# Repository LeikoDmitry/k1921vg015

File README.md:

# Микроконтроллер К1921ВГ015 на базе ядра архитектуры RISC-V

Отладочная плата микроконтроллера K1921VG015

## Номиналы конденсаторов
- C1 - 47uf
- C2 - 0.1uf,
- C3 / C5 - 22uf
- C6 / C9 - 20pf
- C10 / C14 - 0.1uf

## Номиналы индуктивностей L1 - L4 и резистора R10
- R10 = 100/300ом

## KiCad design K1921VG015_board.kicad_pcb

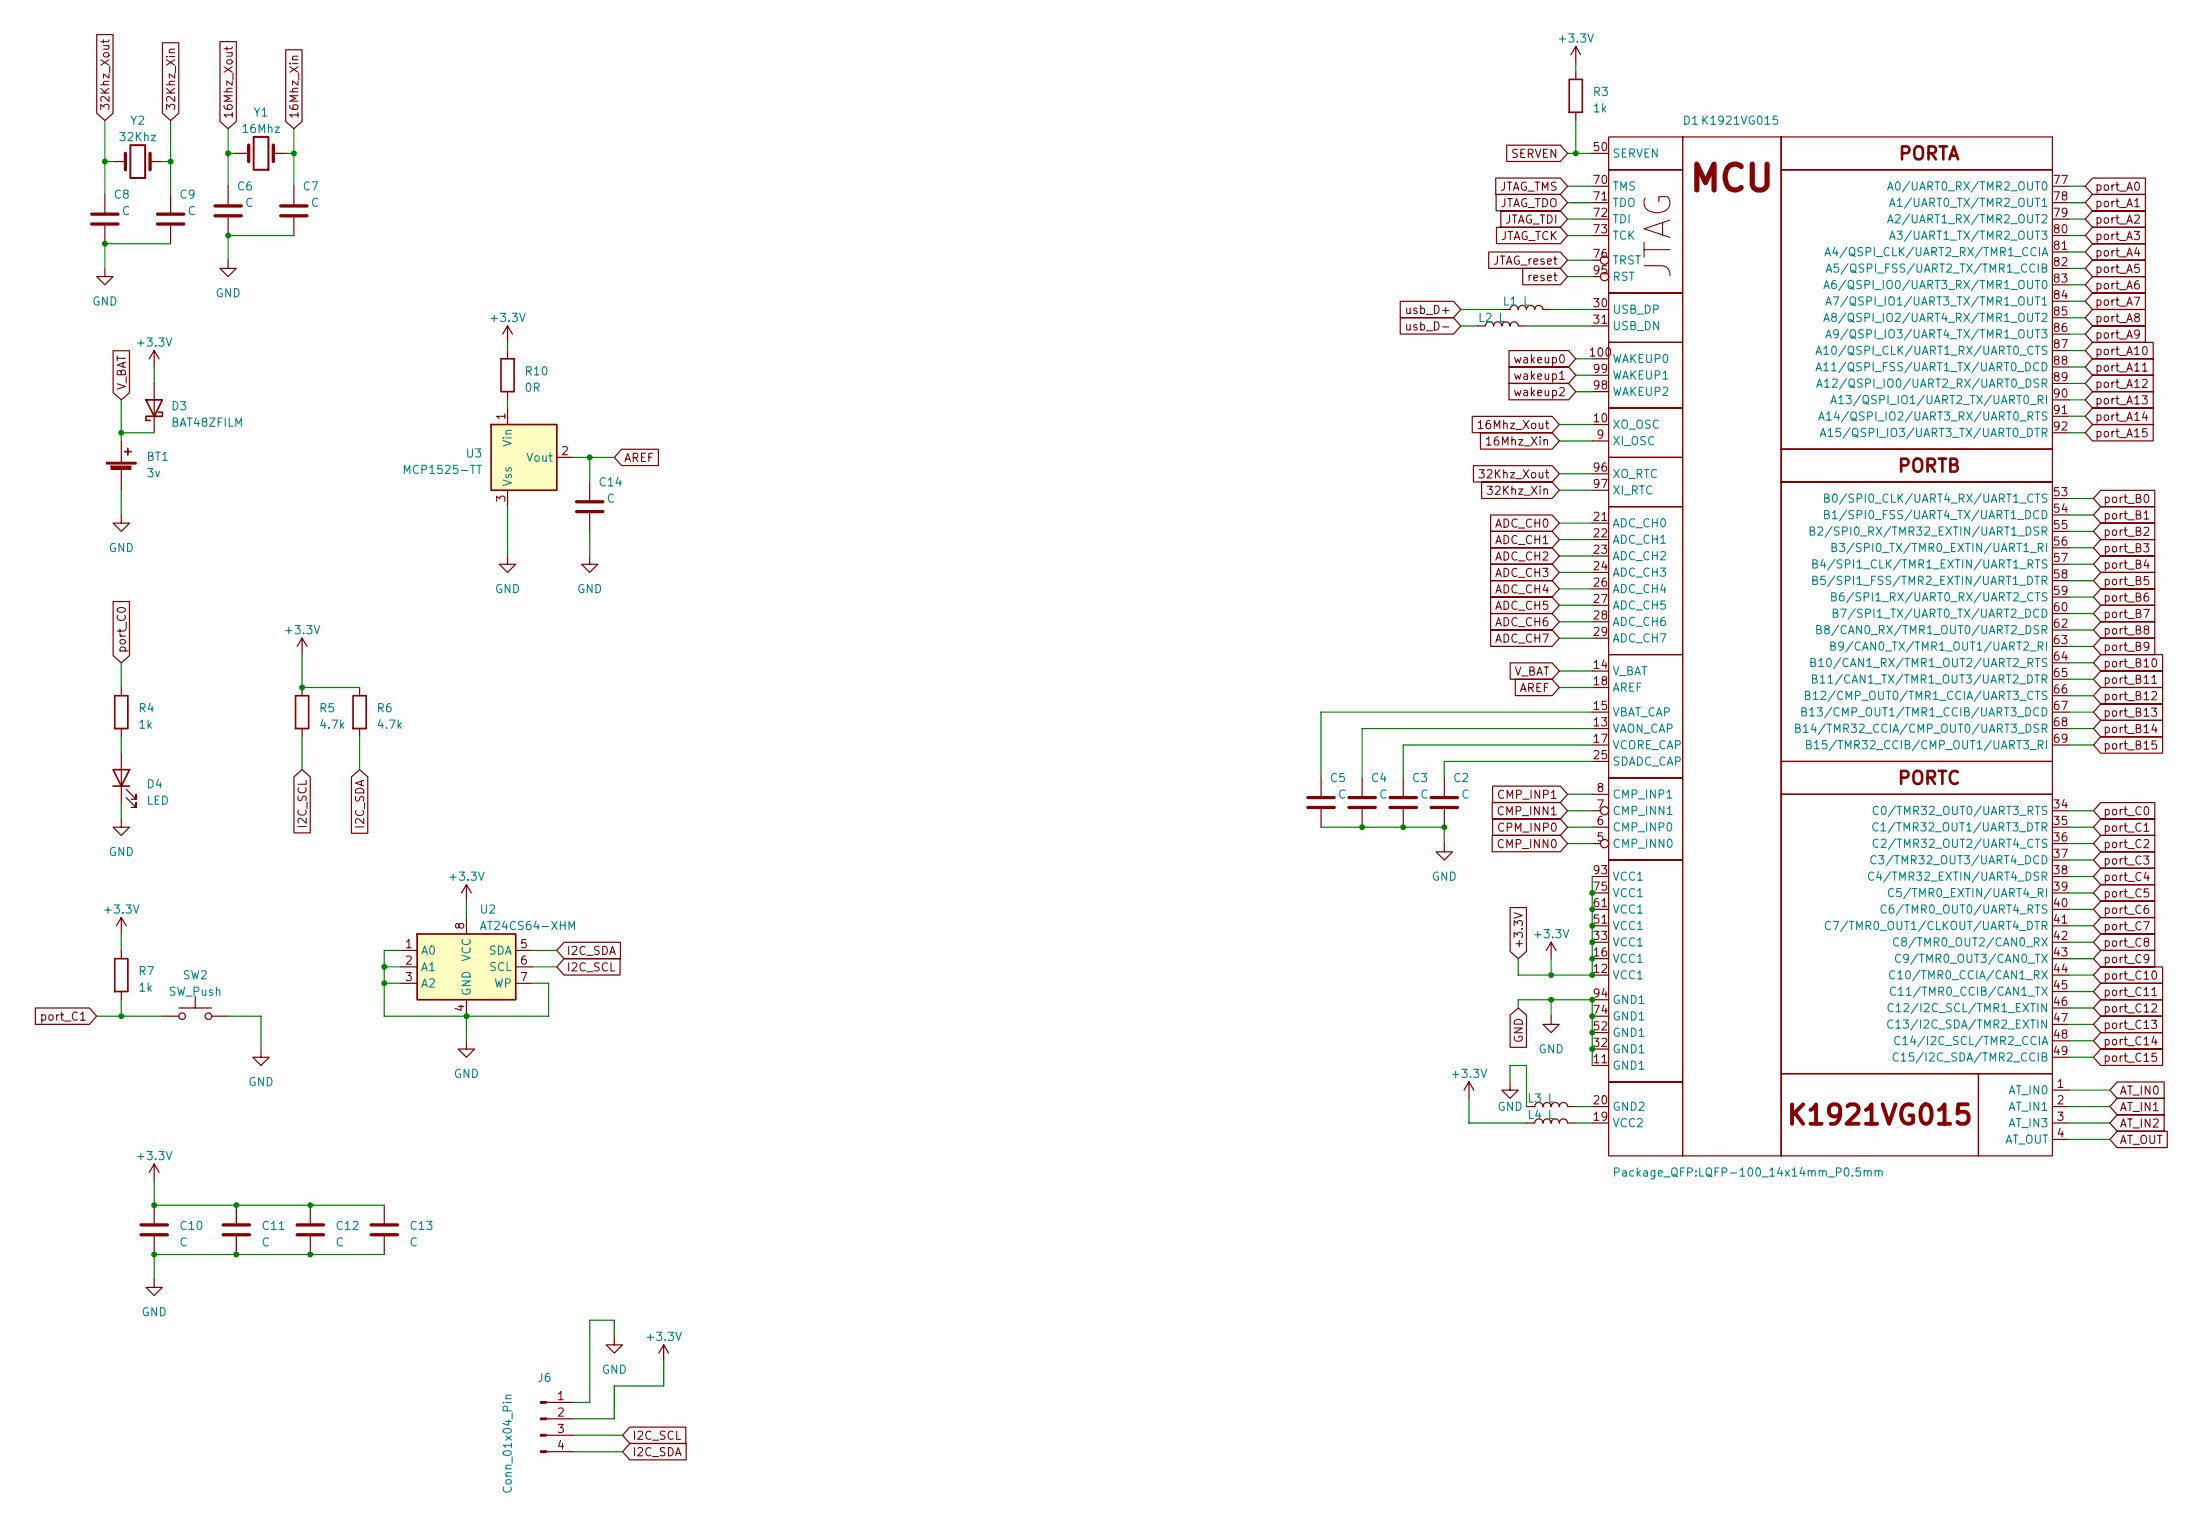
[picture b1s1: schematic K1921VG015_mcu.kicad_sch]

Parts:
BT1: 3v; BatteryHolder_Keystone_1058_1x2032
C2, C6, C7, C8, C9, C10, C11, C12, C13, C14: C; C_0805_2012Metric
C3, C4, C5: C; CP_EIA-3216-18_Kemet-A
D1: K1921VG015; LQFP-100_14x14mm_P0.5mm
D3: BAT48ZFILM; D_SOD-123
D4: LED; LED_0805_2012Metric
J6: Conn_01x04_Pin; PinHeader_1x04_P2.54mm_Vertical
L1, L2, L3, L4: L; L_0805_2012Metric
R3, R4, R7: 1k; R_0805_2012Metric
R5, R6: 4.7k; R_0805_2012Metric
R10: 0R; R_0805_2012Metric
SW2: SW_Push; SW_Push_1P1T_NO_6x6mm_H9.5mm
U2: AT24CS64-XHM; TSSOP-8_4.4x3mm_P0.65mm
U3: MCP1525-TT; SOT-23
Y1: 16Mhz; Crystal_SMD_5032-2Pin_5.0x3.2mm
Y2: 32Khz; Crystal_SMD_3215-2Pin_3.2x1.5mm

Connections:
16Mhz_Xin: C7.1, D1.9 (XI_OSC), Y1.1
16Mhz_Xout: C6.1, D1.10 (XO_OSC), Y1.2
32Khz_Xin: C9.1, D1.97 (XI_RTC), Y2.1
32Khz_Xout: C8.1, D1.96 (XO_RTC), Y2.2
+3.3V: C10.1, C11.1, C12.1, C13.1, D1.12 (VCC1), D1.16 (VCC1), D1.33 (VCC1), D1.51 (VCC1), D1.61 (VCC1), D1.75 (VCC1), D1.93 (VCC1), D3.2 (A), J6.2, L4.1, R3.1, R5.1, R6.1, R7.1, R10.2, U2.8 (VCC); also elsewhere on the board
ADC_CH0: D1.21 (ADC_CH0); also elsewhere on the board
ADC_CH1: D1.22 (ADC_CH1); also elsewhere on the board
ADC_CH2: D1.23 (ADC_CH2); also elsewhere on the board
ADC_CH3: D1.24 (ADC_CH3); also elsewhere on the board
ADC_CH4: D1.26 (ADC_CH4); also elsewhere on the board
ADC_CH5: D1.27 (ADC_CH5); also elsewhere on the board
ADC_CH6: D1.28 (ADC_CH6); also elsewhere on the board
ADC_CH7: D1.29 (ADC_CH7); also elsewhere on the board
AREF: C14.1, D1.18 (AREF), U3.2 (Vout)
AT_IN0: D1.1 (AT_IN0); also elsewhere on the board
AT_IN1: D1.2 (AT_IN1); also elsewhere on the board
AT_IN2: D1.3 (AT_IN3); also elsewhere on the board
AT_OUT: D1.4 (AT_OUT); also elsewhere on the board
CMP_INN0: D1.5 (CMP_INN0); also elsewhere on the board
CMP_INN1: D1.7 (CMP_INN1); also elsewhere on the board
CMP_INP1: D1.8 (CMP_INP1); also elsewhere on the board
CPM_INP0: D1.6 (CMP_INP0); also elsewhere on the board
GND: BT1.2 (-), C2.2, C3.2, C4.2, C5.2, C6.2, C7.2, C8.2, C9.2, C10.2, C11.2, C12.2, C13.2, C14.2, D1.11 (GND1), D1.32 (GND1), D1.52 (GND1), D1.74 (GND1), D1.94 (GND1), D4.1 (K), J6.1, L3.1, SW2.2, U2.1 (A0), U2.2 (A1), U2.3 (A2), U2.4 (GND), U2.7 (WP), U3.3 (Vss); also elsewhere on the board
I2C_SCL: J6.3, R5.2, U2.6 (SCL); also elsewhere on the board
I2C_SDA: J6.4, R6.2, U2.5 (SDA); also elsewhere on the board
JTAG_TCK: D1.73 (TCK); also elsewhere on the board
JTAG_TDI: D1.72 (TDI); also elsewhere on the board
JTAG_TDO: D1.71 (TDO); also elsewhere on the board
JTAG_TMS: D1.70 (TMS); also elsewhere on the board
JTAG_reset: D1.76 (TRST); also elsewhere on the board
unnamed: D1.20 (GND2), L3.2
unnamed: C2.1, D1.25 (SDADC_CAP)
unnamed: D1.31 (USB_DN), L2.2
unnamed: D1.30 (USB_DP), L1.2
unnamed: C4.1, D1.13 (VAON_CAP)
unnamed: C5.1, D1.15 (VBAT_CAP)
unnamed: D1.19 (VCC2), L4.2
unnamed: C3.1, D1.17 (VCORE_CAP)
unnamed: D4.2 (A), R4.2
unnamed: R10.1, U3.1 (Vin)
SERVEN: D1.50 (SERVEN), R3.2; also elsewhere on the board
V_BAT: BT1.1 (+), D1.14 (V_BAT), D3.1 (K)
port_A0: D1.77 (A0/UART0_RX/TMR2_OUT0); also elsewhere on the board
port_A1: D1.78 (A1/UART0_TX/TMR2_OUT1); also elsewhere on the board
port_A2: D1.79 (A2/UART1_RX/TMR2_OUT2); also elsewhere on the board
port_A3: D1.80 (A3/UART1_TX/TMR2_OUT3); also elsewhere on the board
port_A4: D1.81 (A4/QSPI_CLK/UART2_RX/TMR1_CCIA); also elsewhere on the board
port_A5: D1.82 (A5/QSPI_FSS/UART2_TX/TMR1_CCIB); also elsewhere on the board
port_A6: D1.83 (A6/QSPI_IO0/UART3_RX/TMR1_OUT0); also elsewhere on the board
port_A7: D1.84 (A7/QSPI_IO1/UART3_TX/TMR1_OUT1); also elsewhere on the board
port_A8: D1.85 (A8/QSPI_IO2/UART4_RX/TMR1_OUT2); also elsewhere on the board
port_A9: D1.86 (A9/QSPI_IO3/UART4_TX/TMR1_OUT3); also elsewhere on the board
port_A10: D1.87 (A10/QSPI_CLK/UART1_RX/UART0_CTS); also elsewhere on the board
port_A11: D1.88 (A11/QSPI_FSS/UART1_TX/UART0_DCD); also elsewhere on the board
port_A12: D1.89 (A12/QSPI_IO0/UART2_RX/UART0_DSR); also elsewhere on the board
port_A13: D1.90 (A13/QSPI_IO1/UART2_TX/UART0_RI); also elsewhere on the board
port_A14: D1.91 (A14/QSPI_IO2/UART3_RX/UART0_RTS); also elsewhere on the board
port_A15: D1.92 (A15/QSPI_IO3/UART3_TX/UART0_DTR); also elsewhere on the board
port_B0: D1.53 (B0/SPI0_CLK/UART4_RX/UART1_CTS); also elsewhere on the board
port_B1: D1.54 (B1/SPI0_FSS/UART4_TX/UART1_DCD); also elsewhere on the board
port_B2: D1.55 (B2/SPI0_RX/TMR32_EXTIN/UART1_DSR); also elsewhere on the board
port_B3: D1.56 (B3/SPI0_TX/TMR0_EXTIN/UART1_RI); also elsewhere on the board
port_B4: D1.57 (B4/SPI1_CLK/TMR1_EXTIN/UART1_RTS); also elsewhere on the board
port_B5: D1.58 (B5/SPI1_FSS/TMR2_EXTIN/UART1_DTR); also elsewhere on the board
port_B6: D1.59 (B6/SPI1_RX/UART0_RX/UART2_CTS); also elsewhere on the board
port_B7: D1.60 (B7/SPI1_TX/UART0_TX/UART2_DCD); also elsewhere on the board
port_B8: D1.62 (B8/CAN0_RX/TMR1_OUT0/UART2_DSR); also elsewhere on the board
port_B9: D1.63 (B9/CAN0_TX/TMR1_OUT1/UART2_RI); also elsewhere on the board
port_B10: D1.64 (B10/CAN1_RX/TMR1_OUT2/UART2_RTS); also elsewhere on the board
port_B11: D1.65 (B11/CAN1_TX/TMR1_OUT3/UART2_DTR); also elsewhere on the board
port_B12: D1.66 (B12/CMP_OUT0/TMR1_CCIA/UART3_CTS); also elsewhere on the board
port_B13: D1.67 (B13/CMP_OUT1/TMR1_CCIB/UART3_DCD); also elsewhere on the board
port_B14: D1.68 (B14/TMR32_CCIA/CMP_OUT0/UART3_DSR); also elsewhere on the board
port_B15: D1.69 (B15/TMR32_CCIB/CMP_OUT1/UART3_RI); also elsewhere on the board
port_C0: D1.34 (С0/TMR32_OUT0/UART3_RTS), R4.1; also elsewhere on the board
port_C1: D1.35 (С1/TMR32_OUT1/UART3_DTR), R7.2, SW2.1; also elsewhere on the board
port_C2: D1.36 (С2/TMR32_OUT2/UART4_CTS); also elsewhere on the board
port_C3: D1.37 (С3/TMR32_OUT3/UART4_DCD); also elsewhere on the board
port_C4: D1.38 (С4/TMR32_EXTIN/UART4_DSR); also elsewhere on the board
port_C5: D1.39 (С5/TMR0_EXTIN/UART4_RI); also elsewhere on the board
port_C6: D1.40 (С6/TMR0_OUT0/UART4_RTS); also elsewhere on the board
port_C7: D1.41 (С7/TMR0_OUT1/CLKOUT/UART4_DTR); also elsewhere on the board
port_C8: D1.42 (С8/TMR0_OUT2/CAN0_RX); also elsewhere on the board
port_C9: D1.43 (С9/TMR0_OUT3/CAN0_TX); also elsewhere on the board
port_C10: D1.44 (С10/TMR0_CCIA/CAN1_RX); also elsewhere on the board
port_C11: D1.45 (С11/TMR0_CCIB/CAN1_TX); also elsewhere on the board
port_C12: D1.46 (С12/I2C_SCL/TMR1_EXTIN); also elsewhere on the board
port_C13: D1.47 (С13/I2C_SDA/TMR2_EXTIN); also elsewhere on the board
port_C14: D1.48 (С14/I2C_SCL/TMR2_CCIA); also elsewhere on the board
port_C15: D1.49 (С15/I2C_SDA/TMR2_CCIB); also elsewhere on the board
reset: D1.95 (RST); also elsewhere on the board
usb_D+: L1.1; also elsewhere on the board
usb_D-: L2.1; also elsewhere on the board
wakeup0: D1.100 (WAKEUP0); also elsewhere on the board
wakeup1: D1.99 (WAKEUP1); also elsewhere on the board
wakeup2: D1.98 (WAKEUP2); also elsewhere on the board

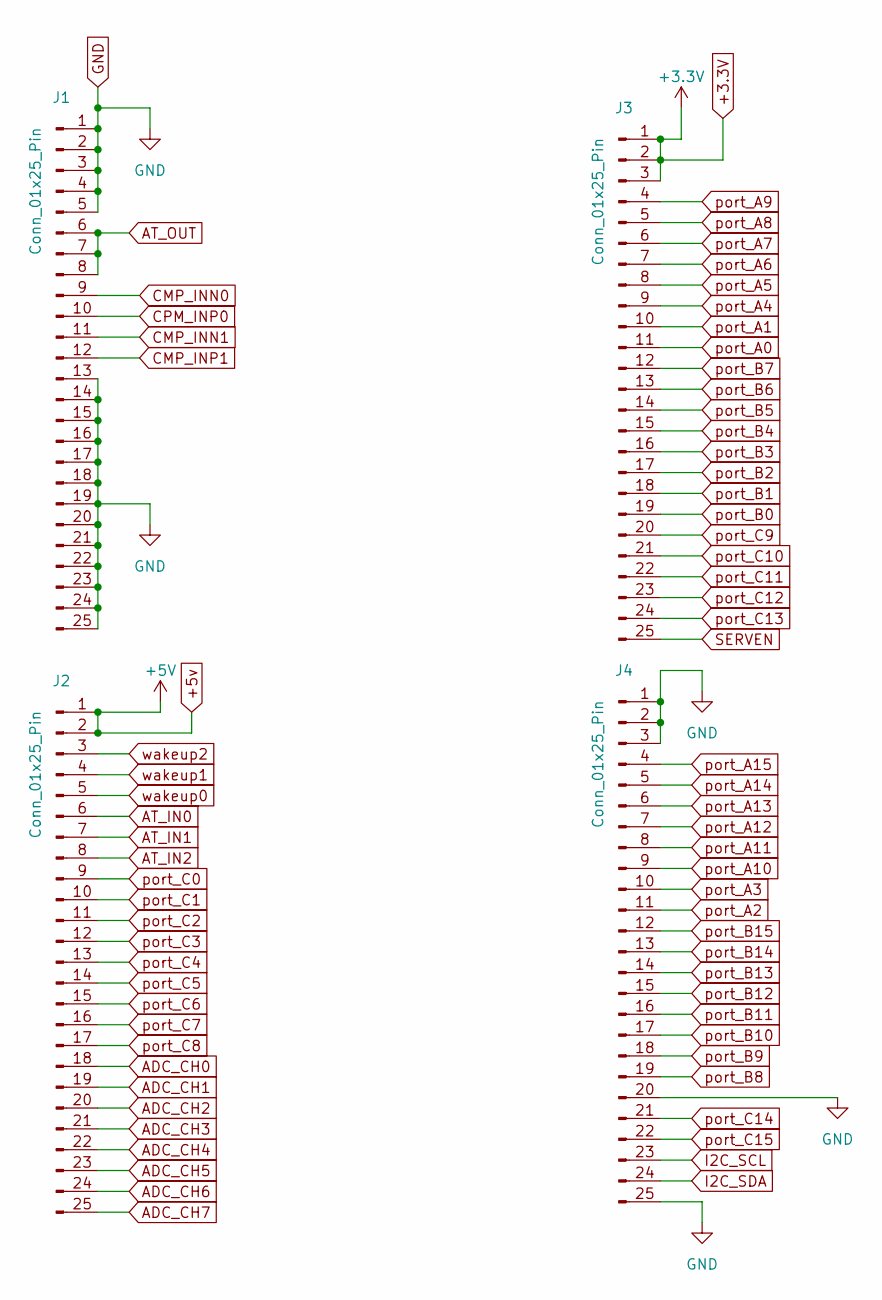
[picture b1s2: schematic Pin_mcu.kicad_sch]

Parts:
J1, J2, J3, J4: Conn_01x25_Pin; PinHeader_1x25_P2.54mm_Vertical

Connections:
+3.3V: J3.1, J3.2, J3.3; also elsewhere on the board
+5v: J2.1, J2.2; also elsewhere on the board
ADC_CH0: J2.18; also elsewhere on the board
ADC_CH1: J2.19; also elsewhere on the board
ADC_CH2: J2.20; also elsewhere on the board
ADC_CH3: J2.21; also elsewhere on the board
ADC_CH4: J2.22; also elsewhere on the board
ADC_CH5: J2.23; also elsewhere on the board
ADC_CH6: J2.24; also elsewhere on the board
ADC_CH7: J2.25; also elsewhere on the board
AT_IN0: J2.6; also elsewhere on the board
AT_IN1: J2.7; also elsewhere on the board
AT_IN2: J2.8; also elsewhere on the board
AT_OUT: J1.6, J1.7, J1.8; also elsewhere on the board
CMP_INN0: J1.9; also elsewhere on the board
CMP_INN1: J1.11; also elsewhere on the board
CMP_INP1: J1.12; also elsewhere on the board
CPM_INP0: J1.10; also elsewhere on the board
GND: J1.1, J1.2, J1.3, J1.4, J1.5, J1.13, J1.14, J1.15, J1.16, J1.17, J1.18, J1.19, J1.20, J1.21, J1.22, J1.23, J1.24, J1.25, J4.1, J4.2, J4.3, J4.20, J4.25; also elsewhere on the board
I2C_SCL: J4.23; also elsewhere on the board
I2C_SDA: J4.24; also elsewhere on the board
SERVEN: J3.25; also elsewhere on the board
port_A0: J3.11; also elsewhere on the board
port_A1: J3.10; also elsewhere on the board
port_A2: J4.11; also elsewhere on the board
port_A3: J4.10; also elsewhere on the board
port_A4: J3.9; also elsewhere on the board
port_A5: J3.8; also elsewhere on the board
port_A6: J3.7; also elsewhere on the board
port_A7: J3.6; also elsewhere on the board
port_A8: J3.5; also elsewhere on the board
port_A9: J3.4; also elsewhere on the board
port_A10: J4.9; also elsewhere on the board
port_A11: J4.8; also elsewhere on the board
port_A12: J4.7; also elsewhere on the board
port_A13: J4.6; also elsewhere on the board
port_A14: J4.5; also elsewhere on the board
port_A15: J4.4; also elsewhere on the board
port_B0: J3.19; also elsewhere on the board
port_B1: J3.18; also elsewhere on the board
port_B2: J3.17; also elsewhere on the board
port_B3: J3.16; also elsewhere on the board
port_B4: J3.15; also elsewhere on the board
port_B5: J3.14; also elsewhere on the board
port_B6: J3.13; also elsewhere on the board
port_B7: J3.12; also elsewhere on the board
port_B8: J4.19; also elsewhere on the board
port_B9: J4.18; also elsewhere on the board
port_B10: J4.17; also elsewhere on the board
port_B11: J4.16; also elsewhere on the board
port_B12: J4.15; also elsewhere on the board
port_B13: J4.14; also elsewhere on the board
port_B14: J4.13; also elsewhere on the board
port_B15: J4.12; also elsewhere on the board
port_C0: J2.9; also elsewhere on the board
port_C1: J2.10; also elsewhere on the board
port_C2: J2.11; also elsewhere on the board
port_C3: J2.12; also elsewhere on the board
port_C4: J2.13; also elsewhere on the board
port_C5: J2.14; also elsewhere on the board
port_C6: J2.15; also elsewhere on the board
port_C7: J2.16; also elsewhere on the board
port_C8: J2.17; also elsewhere on the board
port_C9: J3.20; also elsewhere on the board
port_C10: J3.21; also elsewhere on the board
port_C11: J3.22; also elsewhere on the board
port_C12: J3.23; also elsewhere on the board
port_C13: J3.24; also elsewhere on the board
port_C14: J4.21; also elsewhere on the board
port_C15: J4.22; also elsewhere on the board
wakeup0: J2.5; also elsewhere on the board
wakeup1: J2.4; also elsewhere on the board
wakeup2: J2.3; also elsewhere on the board

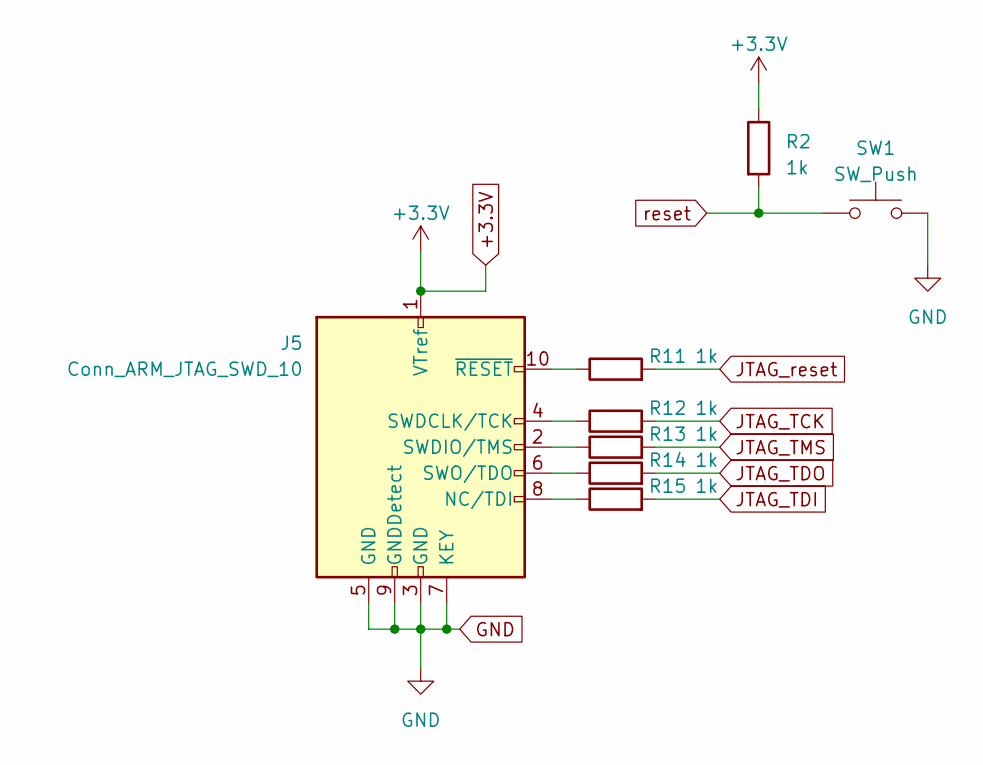
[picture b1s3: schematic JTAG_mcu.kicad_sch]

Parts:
J5: Conn_ARM_JTAG_SWD_10; PinHeader_2x05_P2.54mm_Vertical
R2, R11, R12, R13, R14, R15: 1k; R_0805_2012Metric
SW1: SW_Push; SW_Push_SPST_NO_Alps_SKRK

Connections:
+3.3V: J5.1 (VTref), R2.1; also elsewhere on the board
GND: J5.3 (GND), J5.5 (GND), J5.7 (KEY), J5.9 (GNDDetect), SW1.2; also elsewhere on the board
JTAG_TCK: R12.2; also elsewhere on the board
JTAG_TDI: R15.2; also elsewhere on the board
JTAG_TDO: R14.2; also elsewhere on the board
JTAG_TMS: R13.2; also elsewhere on the board
JTAG_reset: R11.2; also elsewhere on the board
unnamed: J5.8 (NC/TDI), R15.1
unnamed: J5.4 (SWDCLK/TCK), R12.1
unnamed: J5.2 (SWDIO/TMS), R13.1
unnamed: J5.6 (SWO/TDO), R14.1
unnamed: J5.10 (~RESET), R11.1
reset: R2.2, SW1.1; also elsewhere on the board

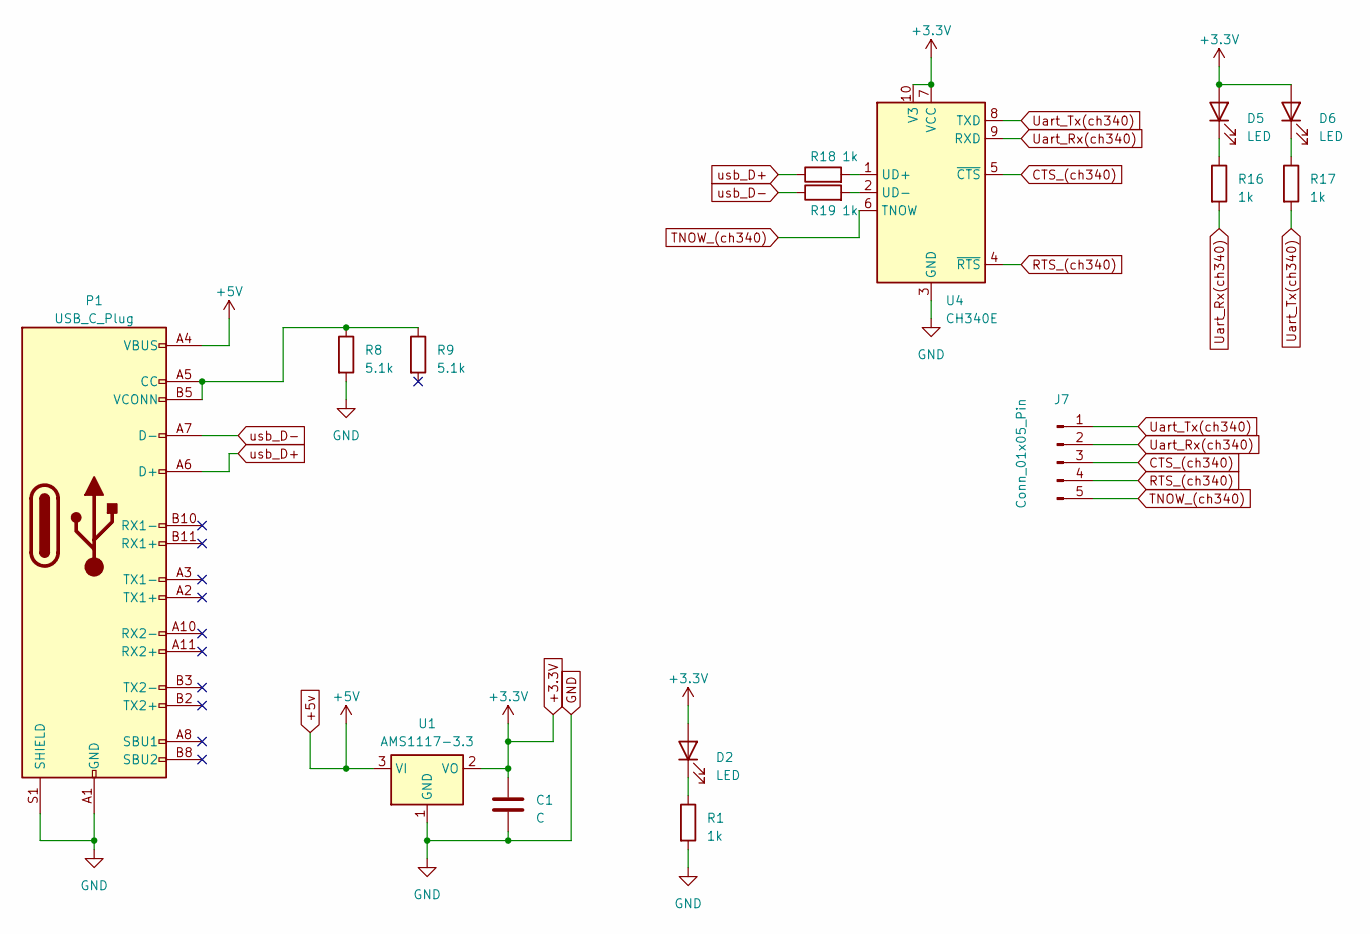
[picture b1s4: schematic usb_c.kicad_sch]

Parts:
C1: C; CP_EIA-3528-12_Kemet-T
D2, D5, D6: LED; LED_0805_2012Metric
J7: Conn_01x05_Pin; PinHeader_1x05_P2.54mm_Vertical
P1: USB_C_Plug; USB_C_Receptacle_G-Switch_GT-USB-7010ASV
R1, R16, R17, R18, R19: 1k; R_0805_2012Metric
R8, R9: 5.1k; R_0805_2012Metric
U1: AMS1117-3.3; SOT-223-3_TabPin2
U4: CH340E; MSOP-10_3x3mm_P0.5mm

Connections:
+3.3V: C1.1, D2.2 (A), D5.2 (A), D6.2 (A), U1.2 (VO), U4.7 (VCC), U4.10 (V3); also elsewhere on the board
+5v: P1.A4 (VBUS), P1.A9 (VBUS), P1.B4 (VBUS), P1.B9 (VBUS), U1.3 (VI); also elsewhere on the board
CTS_(ch340): J7.3, U4.5 (~CTS)
GND: C1.2, P1.A1 (GND), P1.A12 (GND), P1.B1 (GND), P1.B12 (GND), P1.S1 (SHIELD), R1.2, R8.2, U1.1 (GND), U4.3 (GND); also elsewhere on the board
unnamed: D2.1 (K), R1.1
unnamed: D5.1 (K), R16.1
unnamed: D6.1 (K), R17.1
unnamed: P1.A5 (CC), P1.B5 (VCONN), R8.1, R9.1
unnamed: R18.2, U4.1 (UD+)
unnamed: R19.2, U4.2 (UD-)
RTS_(ch340): J7.4, U4.4 (~RTS)
TNOW_(ch340): J7.5, U4.6 (TNOW)
Uart_Rx(ch340): J7.2, R16.2, U4.9 (RXD)
Uart_Tx(ch340): J7.1, R17.2, U4.8 (TXD)
usb_D+: P1.A6 (D+), R18.1; also elsewhere on the board
usb_D-: P1.A7 (D-), R19.1; also elsewhere on the board

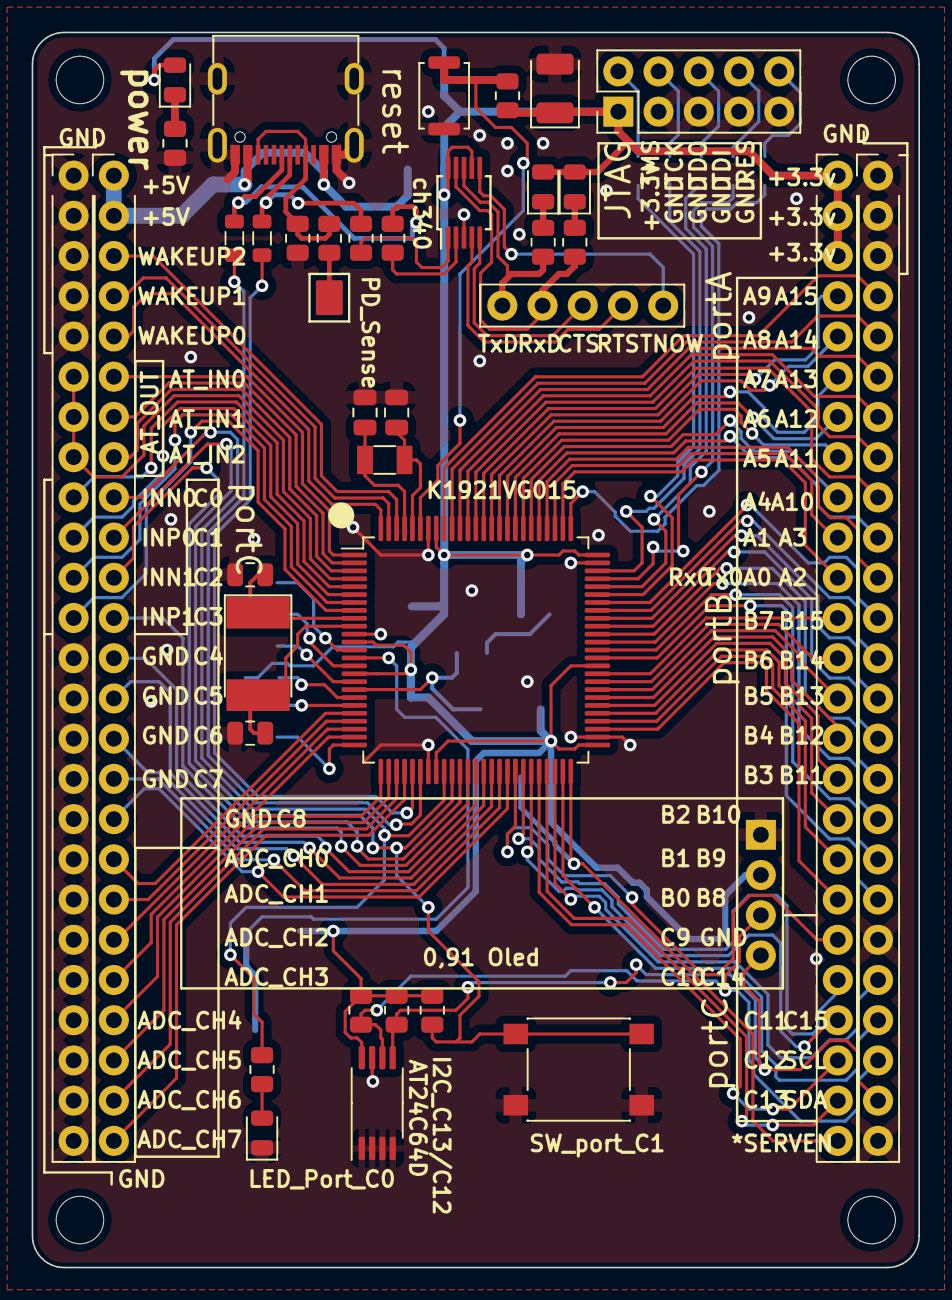
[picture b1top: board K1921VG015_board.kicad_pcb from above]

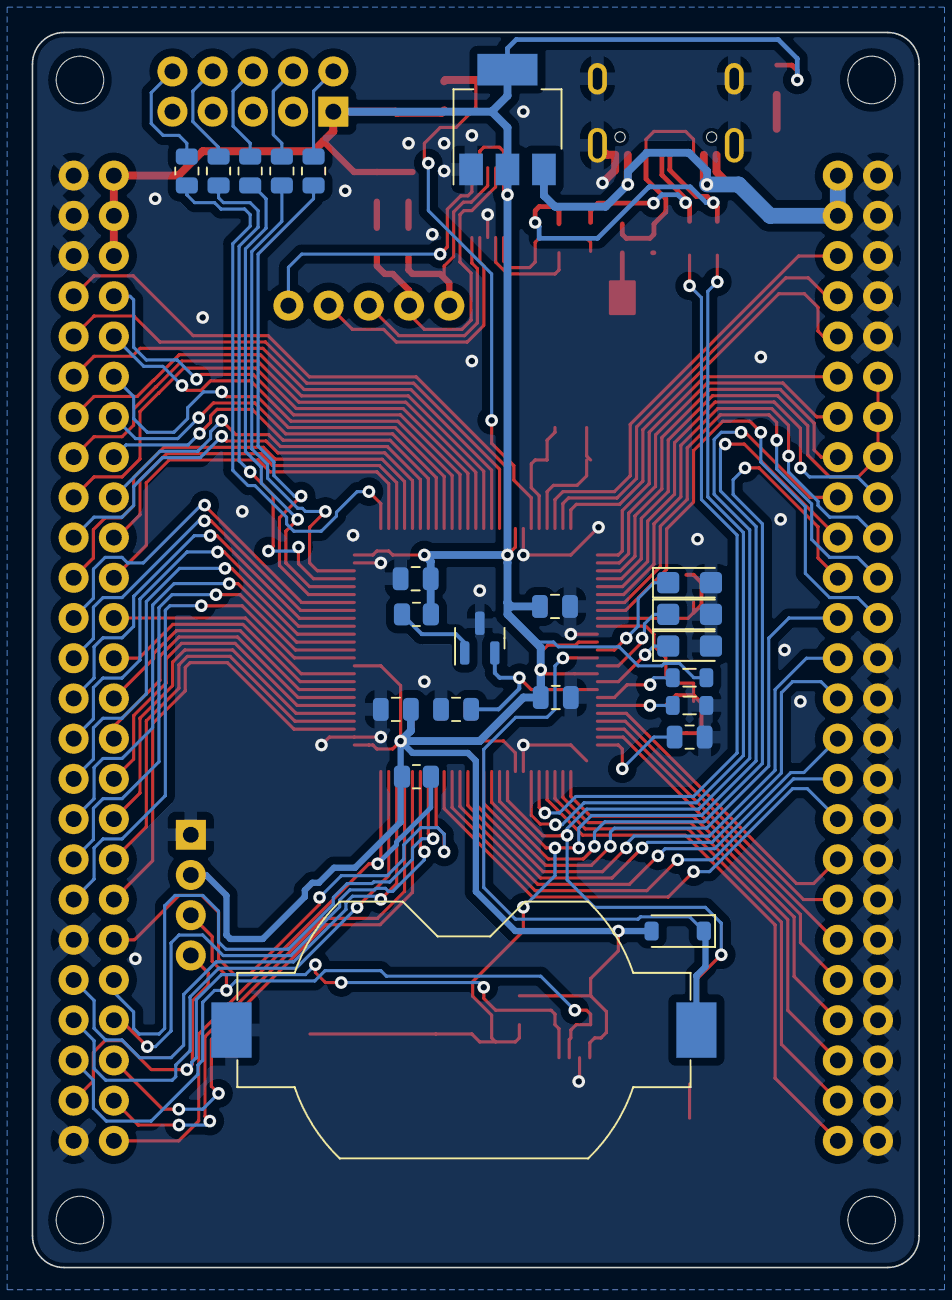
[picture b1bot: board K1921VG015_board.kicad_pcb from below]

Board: 2 copper layers, 56.0 x 78.0 mm, 60 parts (22 on the bottom side), 113 nets.

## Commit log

2025-04-16 Добавлены файлы fp-info-cache, JTAG_mcu.kicad_sch, K1921VG015_board.kicad_pcb, K1921VG015_board.kicad_prl, K1921VG015_board.kicad_pro, K1921VG015_board.kicad_sch, K1921VG015_board-backups.zip, K1921V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
2025-04-16 Добавлены файлы GdUvem2mzhg.jpg, GvVZwkPapc4.jpg
2025-05-30 Create LICENSE
2025-05-30 Added Doc
2025-06-26 Создан файл README.md
2025-06-26 Обновлен файл README.md
